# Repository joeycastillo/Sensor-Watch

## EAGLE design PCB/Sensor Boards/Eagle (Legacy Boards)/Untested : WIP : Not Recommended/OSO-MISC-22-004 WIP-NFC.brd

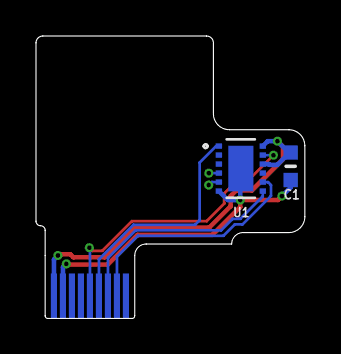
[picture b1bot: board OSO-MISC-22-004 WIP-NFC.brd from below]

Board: 2 copper layers, 14.9 x 15.7 mm, 3 parts (2 on the bottom side), 6 nets.

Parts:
C1: 1uF; _0603MP
U1: ST25DV64K-JFR8D3; UFDFPN12_3X3_STM
U$3: FH19C-9S-0.5SH_10-FFC; FH19C9S05SH10-FFC

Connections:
3.3V: C1.1, U1.10, U1.12, U$3.1
GND: C1.2, U1.6, U1.13, U$3.2
INT: U1.11, U$3.5
LPD: U1.1, U$3.6
SCL: U1.8, U$3.8
SDA: U1.7, U$3.7

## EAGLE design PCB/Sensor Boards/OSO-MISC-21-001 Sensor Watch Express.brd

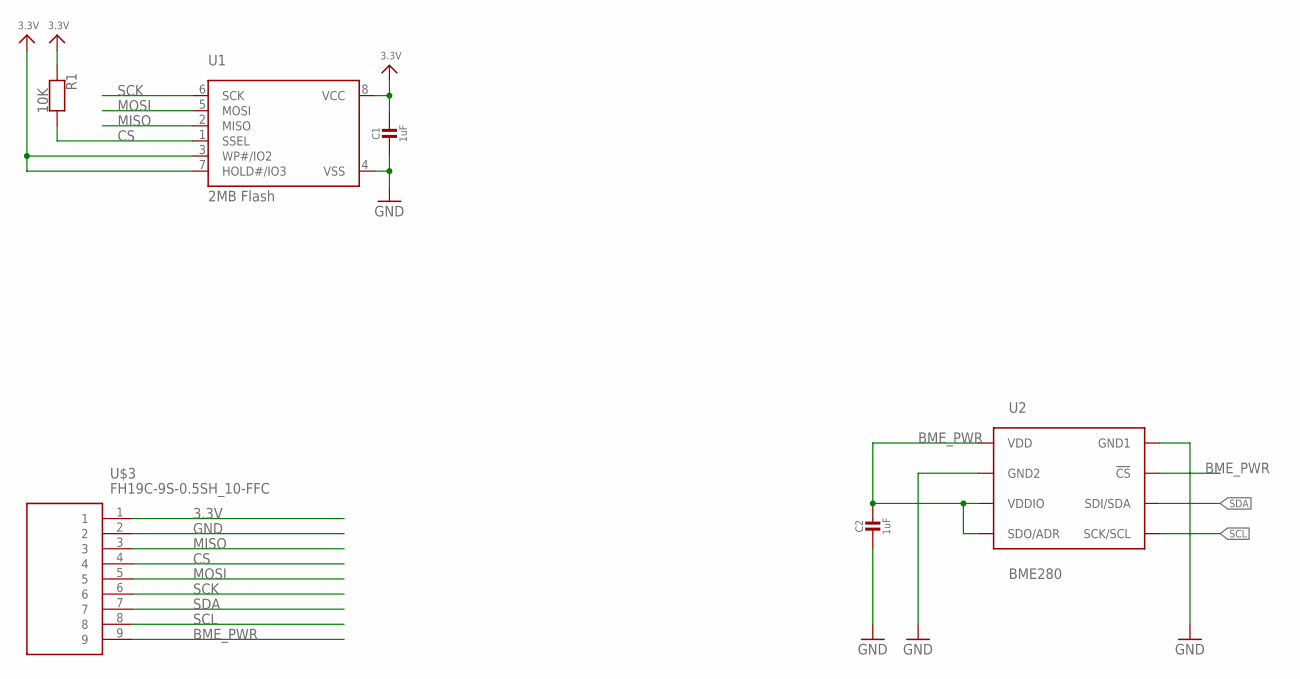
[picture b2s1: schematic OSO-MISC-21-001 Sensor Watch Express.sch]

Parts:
C1, C2: 1uF; _0402MP
R1: 10K; _0402MP
U1: 2MB Flash; USON8
U2: BME280; BME280_LGA
U$3: FH19C-9S-0.5SH_10-FFC; FH19C9S05SH10-FFC

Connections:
3.3V: C1.1, R1.1, U1.3 (WP#/IO2), U1.7 (HOLD#/IO3), U1.8 (VCC), U$3.1
BME_PWR: C2.1, U2.P$2 (!CS), U2.P$5 (SDO/ADR), U2.P$6 (VDDIO), U2.P$8 (VDD), U$3.9
CS: R1.2, U1.1 (SSEL), U$3.4
GND: C1.2, C2.2, U1.4 (VSS), U2.P$1 (GND1), U2.P$7 (GND2), U$3.2
MISO: U1.2 (MISO), U$3.3
MOSI: U1.5 (MOSI), U$3.5
SCK: U1.6 (SCK), U$3.6
SCL: U2.P$4 (SCK/SCL), U$3.8
SDA: U2.P$3 (SDI/SDA), U$3.7

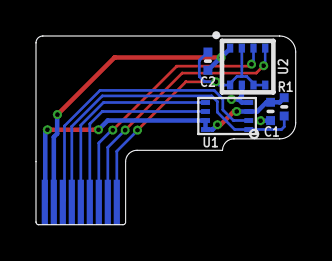
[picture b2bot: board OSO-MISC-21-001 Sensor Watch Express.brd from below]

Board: 2 copper layers, 14.4 x 10.5 mm, 6 parts (5 on the bottom side), 9 nets.

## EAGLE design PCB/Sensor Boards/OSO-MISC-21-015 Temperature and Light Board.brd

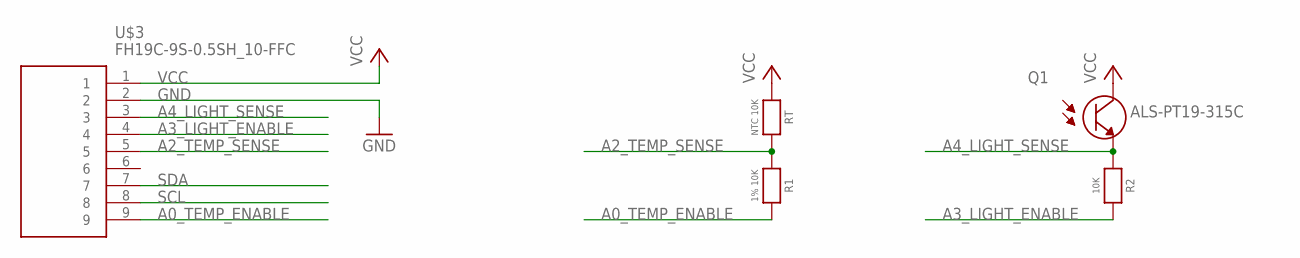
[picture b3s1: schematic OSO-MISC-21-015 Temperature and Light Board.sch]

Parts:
Q1: ALS-PT19-315C; XDCR_ALS-PT19-315C/L177/TR8_REVERSE
R1: 1% 10K; _0603MP
R2: 10K; _0603MP
RT: NTC 10K; _0603
U$3: FH19C-9S-0.5SH_10-FFC; FH19C9S05SH10-FFC

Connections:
A0_TEMP_ENABLE: R1.2, U$3.9
A2_TEMP_SENSE: R1.1, RT.2, U$3.5
A3_LIGHT_ENABLE: R2.2, U$3.4
A4_LIGHT_SENSE: Q1.2 (E), R2.1, U$3.3
GND: U$3.2
SCL: U$3.8
SDA: U$3.7
VCC: Q1.1 (C), RT.1, U$3.1

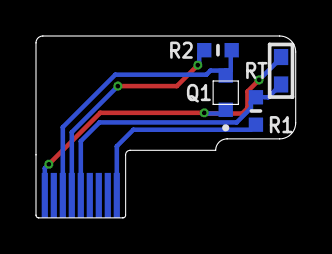
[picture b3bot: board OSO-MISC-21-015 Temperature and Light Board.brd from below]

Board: 2 copper layers, 14.4 x 10.1 mm, 5 parts (4 on the bottom side), 5 nets.

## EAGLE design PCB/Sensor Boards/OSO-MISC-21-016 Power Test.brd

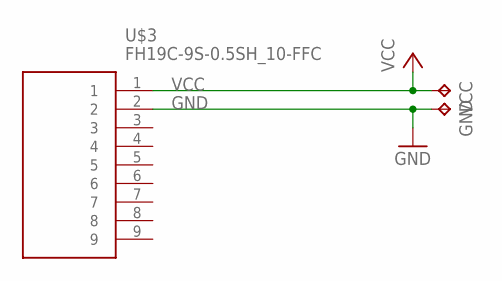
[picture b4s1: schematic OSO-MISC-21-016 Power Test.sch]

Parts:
GND: TPB2,54; B2,54
U$3: FH19C-9S-0.5SH_10-FFC; FH19C9S05SH10-FFC
VCC: TPB2,54; B2,54

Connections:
GND: GND.TP, U$3.2
VCC: U$3.1, VCC.TP

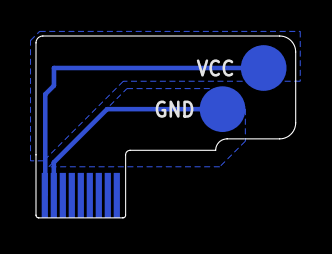
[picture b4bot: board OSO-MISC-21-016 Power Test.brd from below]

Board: 2 copper layers, 14.4 x 10.1 mm, 3 parts (2 on the bottom side), 2 nets.

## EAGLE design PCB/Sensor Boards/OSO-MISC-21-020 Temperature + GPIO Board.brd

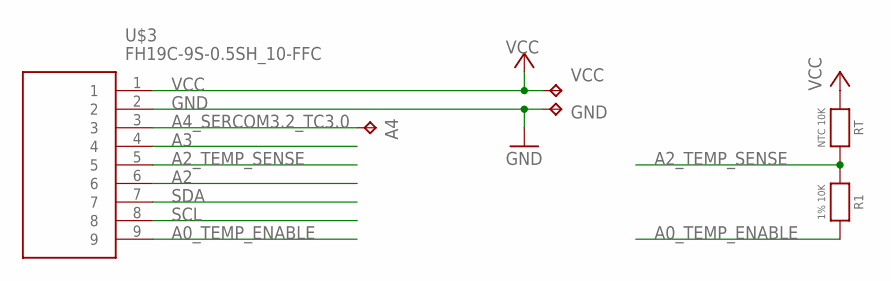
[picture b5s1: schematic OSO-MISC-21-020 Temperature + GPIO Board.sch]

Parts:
A4: TPB1,27; B1,27
GND: TPB1,27; B1,27
R1: 1% 10K; _0603MP
RT: NTC 10K; _0603
U$3: FH19C-9S-0.5SH_10-FFC; FH19C9S05SH10-FFC
VCC: TPB1,27; B1,27

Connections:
A0_TEMP_ENABLE: R1.2, U$3.9
A2: U$3.6
A2_TEMP_SENSE: R1.1, RT.2, U$3.5
A3: U$3.4
A4_SERCOM3.2_TC3.0: A4.TP, U$3.3
GND: GND.TP, U$3.2
SCL: U$3.8
SDA: U$3.7
VCC: RT.1, U$3.1, VCC.TP

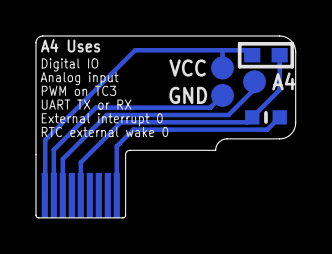
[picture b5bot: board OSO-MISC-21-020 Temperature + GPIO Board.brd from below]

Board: 2 copper layers, 14.4 x 10.1 mm, 6 parts (5 on the bottom side), 5 nets.

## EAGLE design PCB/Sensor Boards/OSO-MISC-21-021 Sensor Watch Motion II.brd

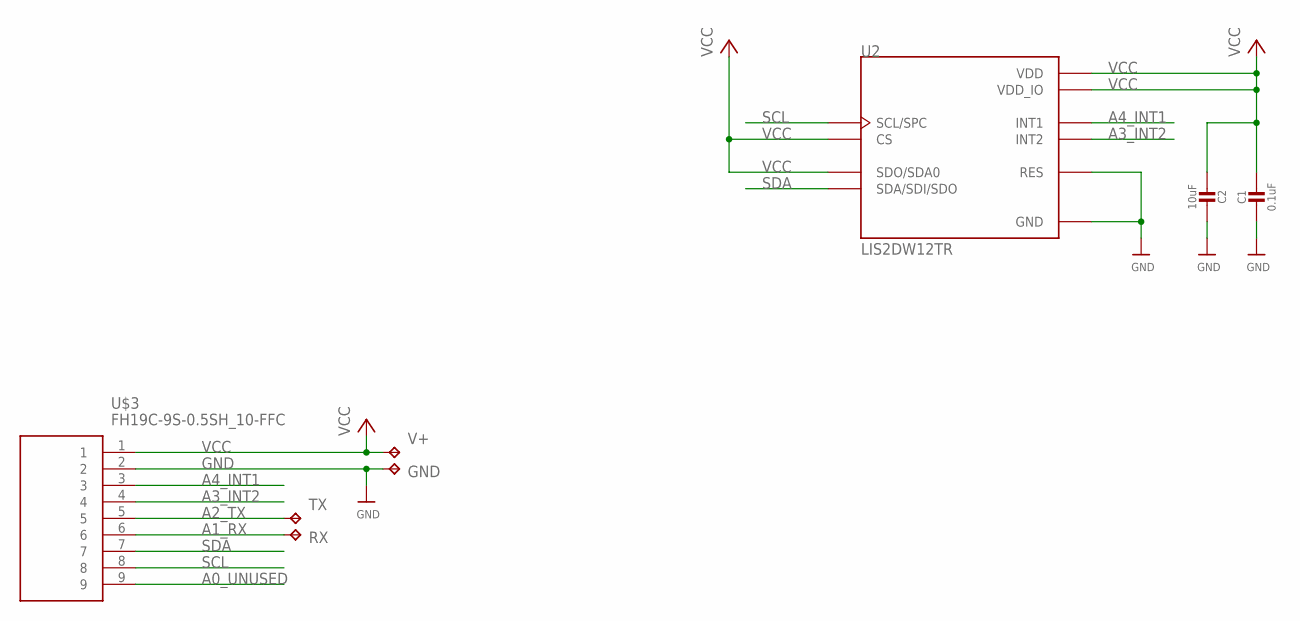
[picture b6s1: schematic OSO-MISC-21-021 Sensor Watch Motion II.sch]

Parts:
C1: 0.1uF; _0603MP
C2: 10uF; _0603MP
GND: TPB1,27; B1,27
RX: TPB1,27; B1,27
TX: TPB1,27; B1,27
U2: LIS2DW12TR; LGA12R50P4X4_200X200X70
U$3: FH19C-9S-0.5SH_10-FFC; FH19C9S05SH10-FFC
V+: TPB1,27; B1,27

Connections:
A0_UNUSED: U$3.9
A1_RX: RX.TP, U$3.6
A2_TX: TX.TP, U$3.5
A3_INT2: U2.11 (INT2), U$3.4
A4_INT1: U2.12 (INT1), U$3.3
GND: C1.2, C2.1, GND.TP, U2.6 (GND), U2.7 (RES), U2.8 (GND), U$3.2
SCL: U2.1 (SCL/SPC), U$3.8
SDA: U2.4 (SDA/SDI/SDO), U$3.7
VCC: C1.1, C2.2, U2.2 (CS), U2.3 (SDO/SDA0), U2.9 (VDD), U2.10 (VDD_IO), U$3.1, V+.TP

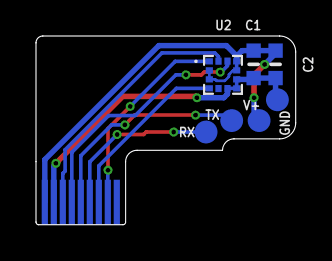
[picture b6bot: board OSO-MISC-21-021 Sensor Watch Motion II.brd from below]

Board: 2 copper layers, 14.4 x 10.5 mm, 8 parts (7 on the bottom side), 8 nets.

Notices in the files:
parts and their libraries:
My Stuff: cc-by-sa 4.0
microbuilder: This work is placed in the public domain, and may be freely used for commercial and non-commercial work with the following conditions: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
COPYRIGHT: Copyright (C) 2021 Ultra Librarian. All rights reserved.
